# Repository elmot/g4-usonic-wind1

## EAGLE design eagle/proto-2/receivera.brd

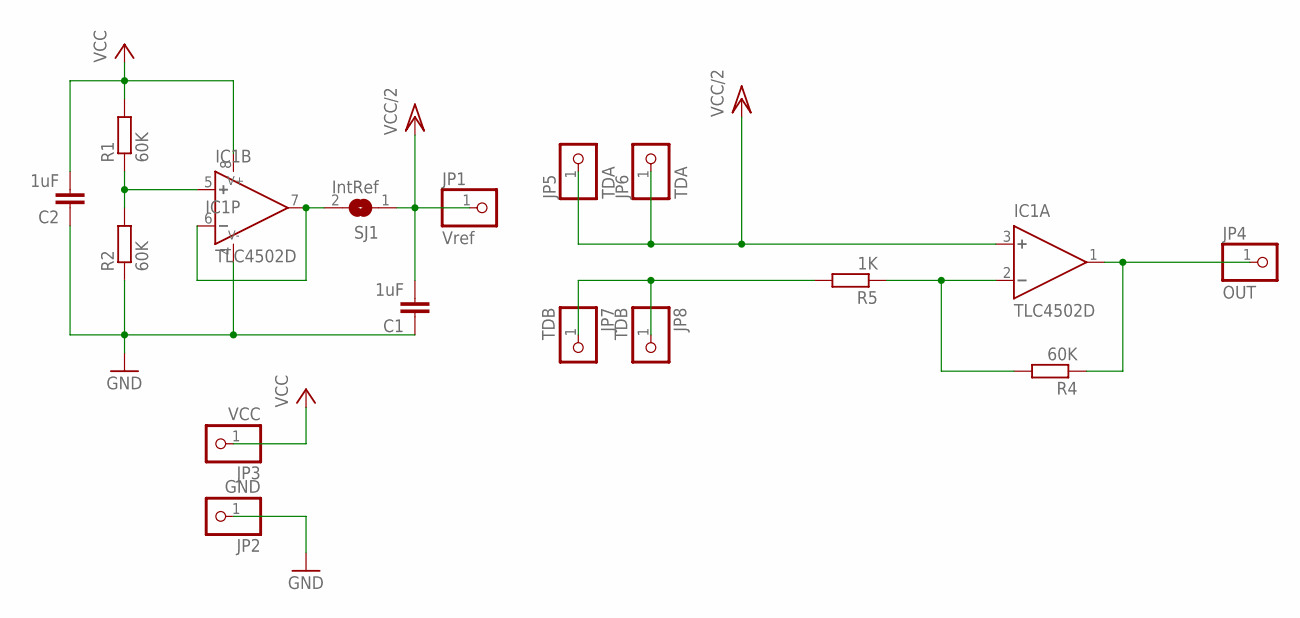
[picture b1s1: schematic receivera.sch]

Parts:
C1, C2: 1uF; C1206
IC1: TLC4502D; D_R-PDSO-G08
JP1: Vref; 1X01
JP2: GND; 1X01
JP3: VCC; 1X01
JP4: OUT; 1X01
JP5, JP6: TDA; 1X01
JP7, JP8: TDB; 1X01
R1, R2, R4: 60K; R1206
R5: 1K; R1206
SJ1: IntRef; SJ

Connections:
GND: C1.1, C2.1, IC1.4 (V-), JP2.1, R2.1
unnamed: IC1.5 (+), R1.1, R2.2
unnamed: IC1.1 (OUT), JP4.1, R4.1
unnamed: JP7.1, JP8.1, R5.2
unnamed: IC1.2 (-), R4.2, R5.1
unnamed: IC1.6 (-), IC1.7 (OUT), SJ1.2
VCC: C2.2, IC1.8 (V+), JP3.1, R1.2
VCC/2: C1.2, IC1.3 (+), JP1.1, JP5.1, JP6.1, SJ1.1

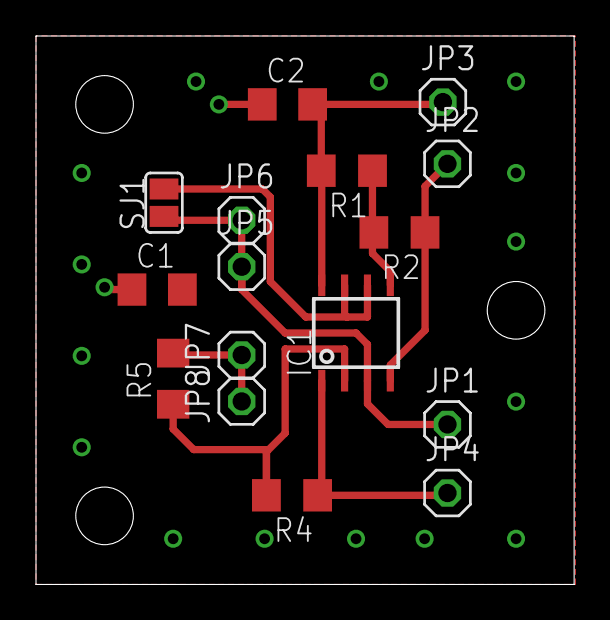
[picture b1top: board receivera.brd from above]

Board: 2 copper layers, 29.9 x 30.5 mm, 16 parts (0 on the bottom side), 8 nets.

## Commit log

2019-11-21 STM32G4 docs
2019-11-21 Small HW changes
2019-11-21 Nucleo docs
2019-11-26 Alter project structure
2019-11-26 SVD(buggy)
2019-11-26 Charts support at debugger
2019-11-26 Code update for DAC/ADC/DMA tests
2019-12-09 Some docs
2020-01-03 Next experiment
2020-01-03 Plywood template
2020-01-07 Opamp test
2020-01-08 First promising results
2020-01-08 Second promising results
2020-03-09 Interferention version works
2020-04-06 Next step
2020-04-19 Before CMSIS DSP
